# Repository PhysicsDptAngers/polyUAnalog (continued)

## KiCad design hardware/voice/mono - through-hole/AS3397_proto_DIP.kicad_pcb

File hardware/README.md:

## Hardware Components of the polyUAnalog System

- **Voice Board**: This is the core component of the project. A voice board is, by itself, an analog monophonic synthesizer. In short, the sound is generated by the AS3397 chip, controlled by an RP2040/RP2530 (Raspberry Pi Pico) microcontroller.

- **Conductor Board**: All voice boards are connected to the conductor board. It receives commands from external sources in MIDI-compatible format and distributes them to the voice boards via the I²C bus.

- **Controller Board**: These are the interface panels of the synthesizer. They typically include potentiometers, encoders, LEDs, and screens used to program and control the synthesizer. The corresponding data is sent to the conductor board via the I²C bus.

- **Power Board**: The synthesizer requires three power rails to operate (+12V, +5V, -5V). We provide a simple design using a USB Type-C power block with Power Delivery support to supply a regulated +12V rail. The +5V and -5V rails are then generated using buck converters.

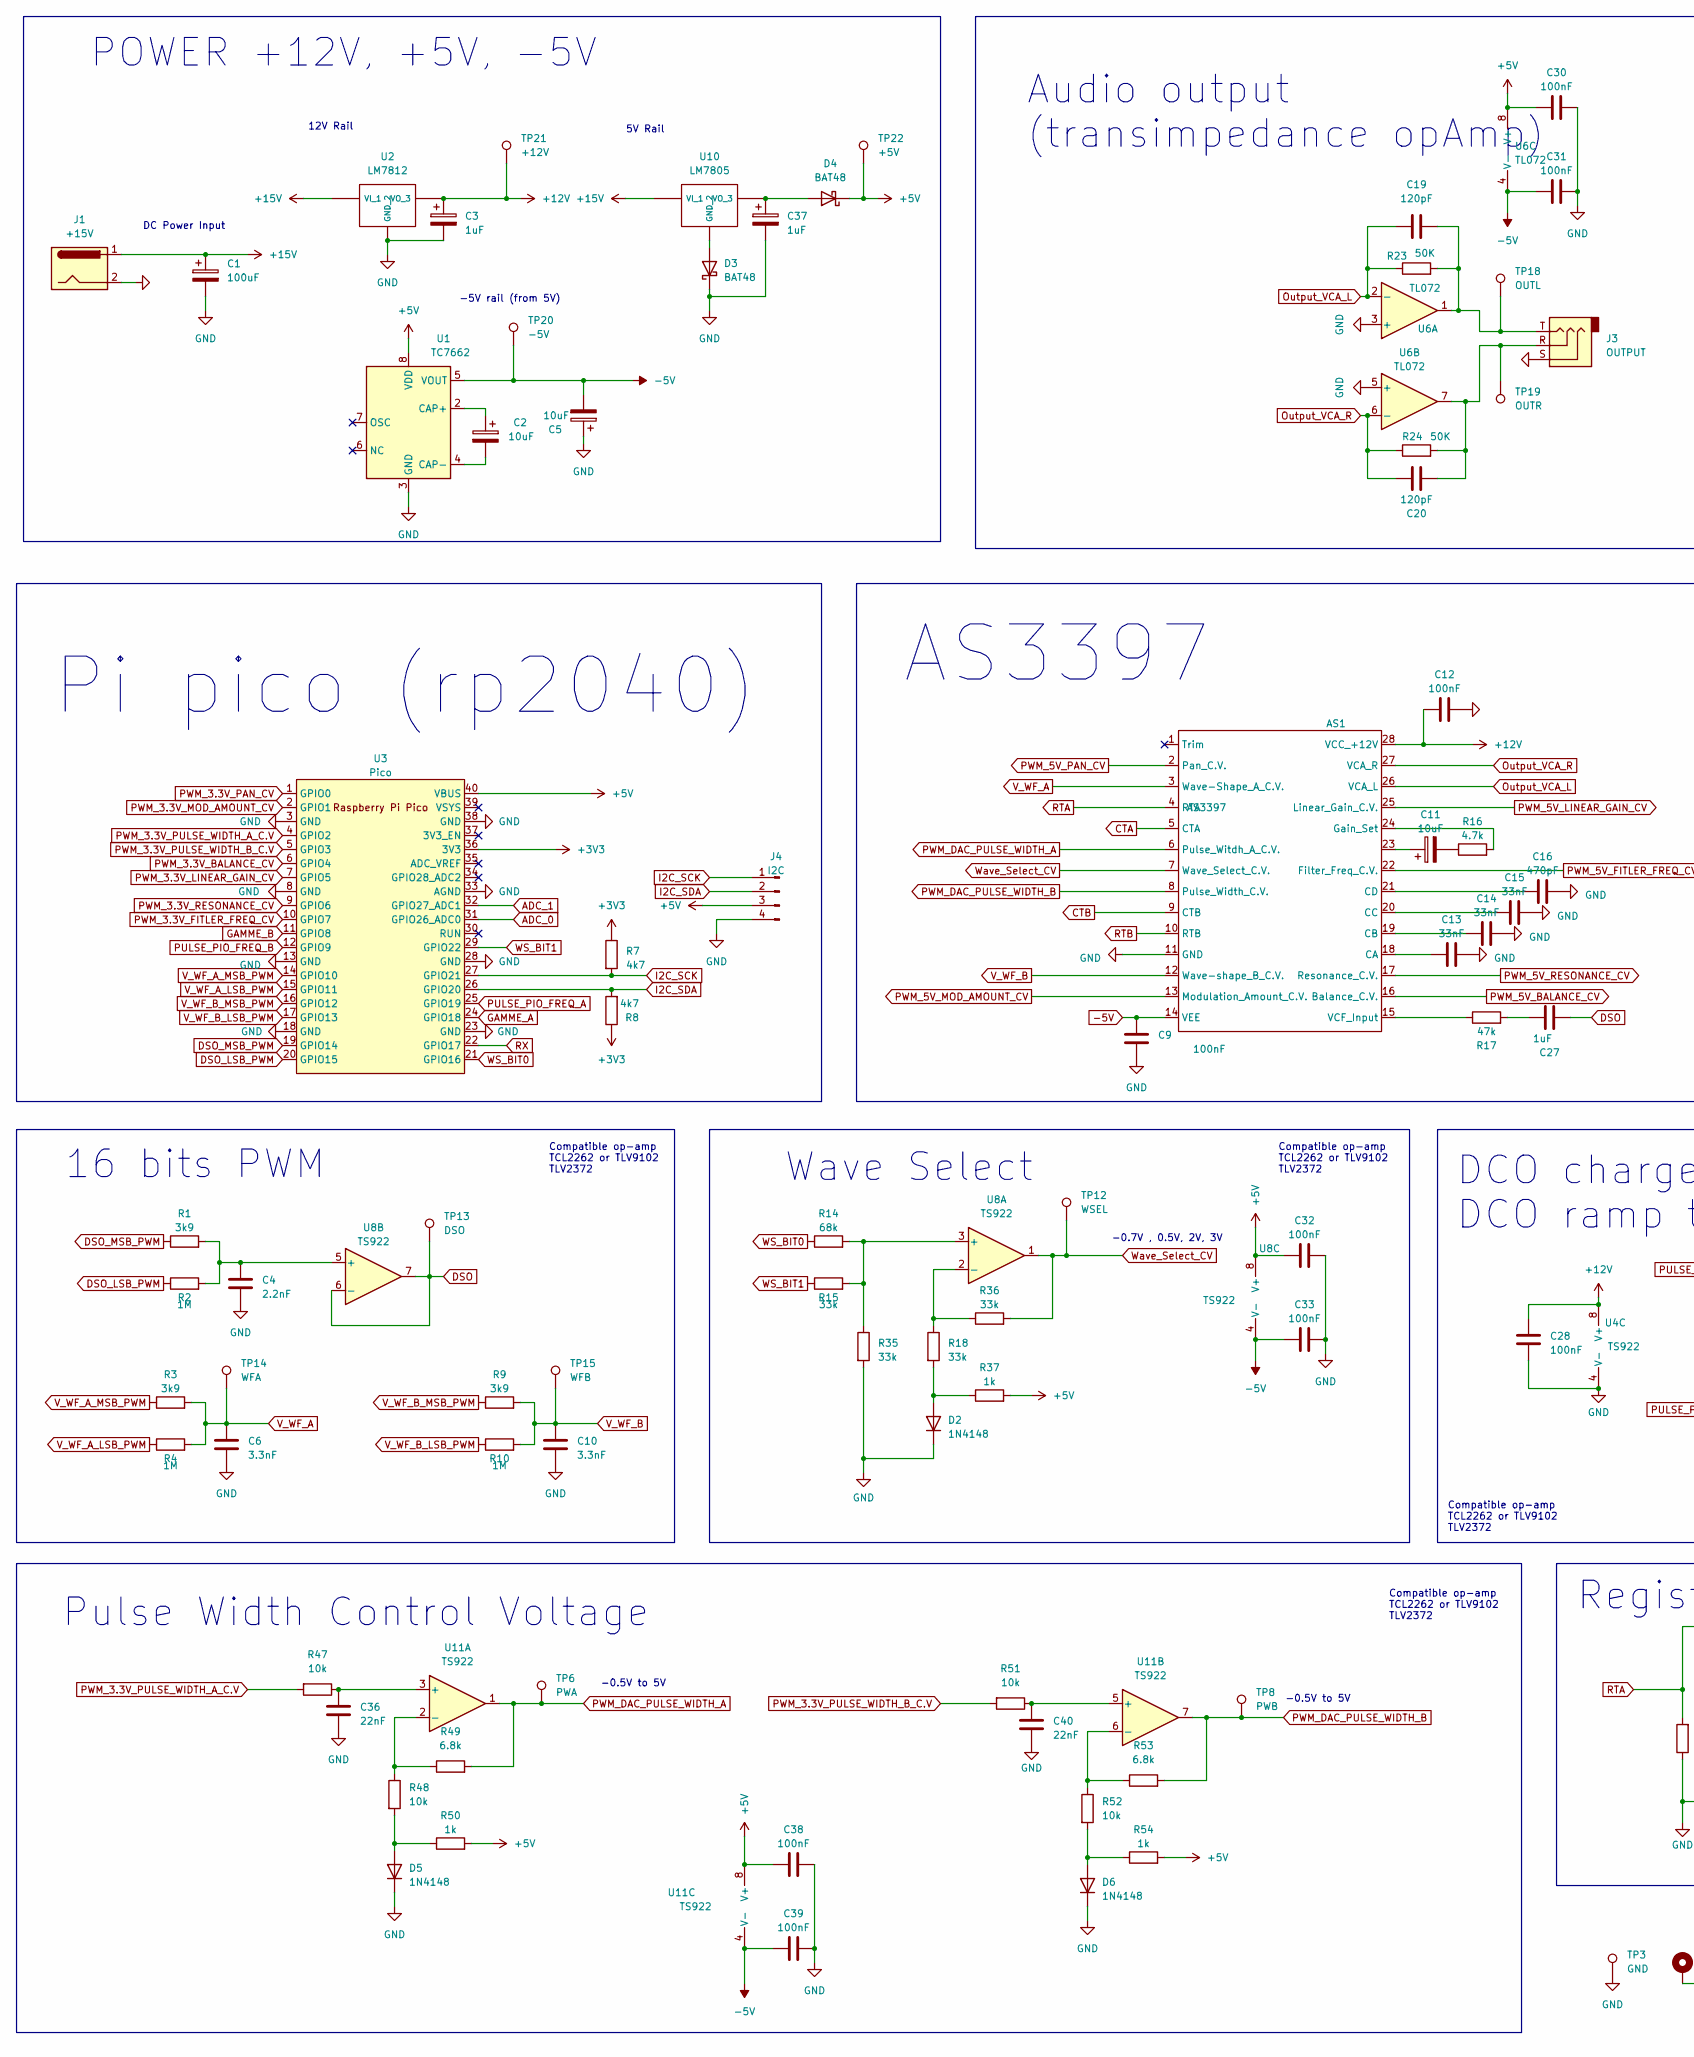
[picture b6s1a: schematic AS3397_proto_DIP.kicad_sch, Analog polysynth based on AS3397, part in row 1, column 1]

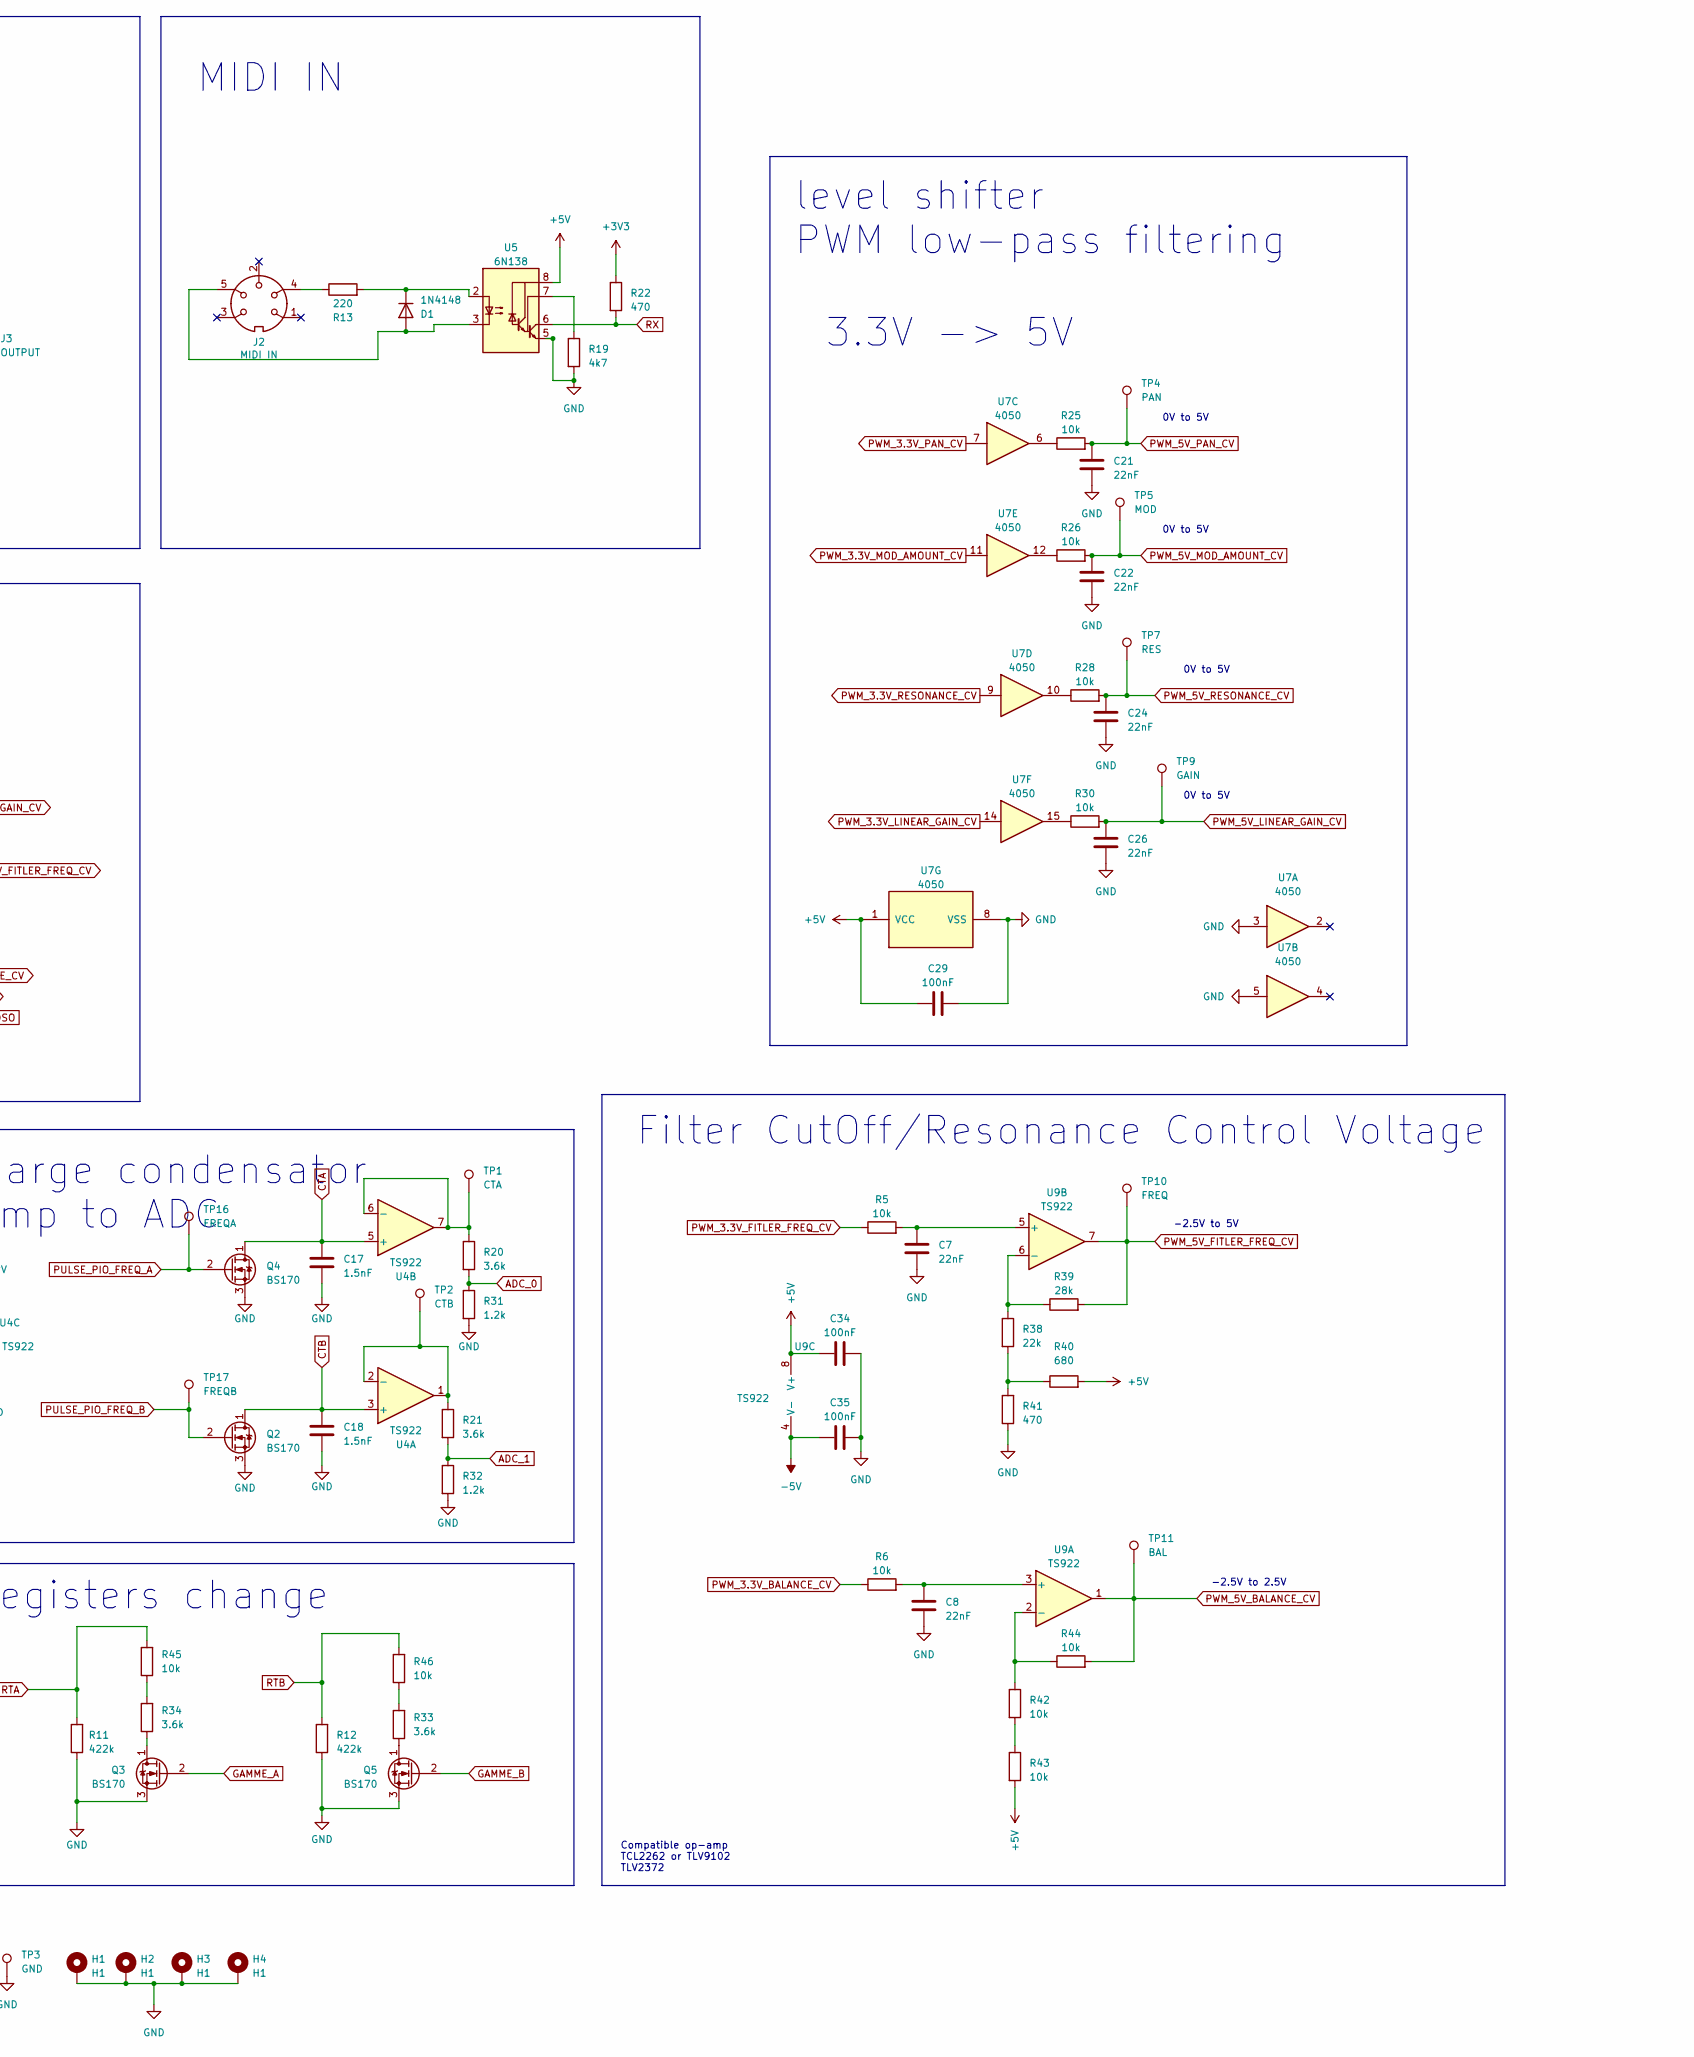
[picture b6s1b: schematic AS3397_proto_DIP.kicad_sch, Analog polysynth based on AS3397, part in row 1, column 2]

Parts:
AS1: AS3397; SOIC-28W_7.5x18.7mm_P1.27mm
C1: 100uF; CP_Radial_D8.0mm_P5.00mm
C2, C5, C11: 10uF; CP_Radial_D5.0mm_P2.50mm
C3, C37: 1uF; CP_Radial_D5.0mm_P2.50mm
C4: 2.2nF; C_Rect_L7.0mm_W2.0mm_P5.00mm
C6, C10: 3.3nF; C_Rect_L7.0mm_W2.0mm_P5.00mm
C7, C8, C21, C22, C24, C26, C36, C40: 22nF; C_Rect_L7.0mm_W2.0mm_P5.00mm
C9, C12, C28, C29, C30, C31, C32, C33, C34, C35, C38, C39: 100nF; C_Rect_L7.0mm_W2.0mm_P5.00mm
C13, C14, C15: 33nF; C_Rect_L7.0mm_W2.0mm_P5.00mm
C16: 470pF; C_Disc_D4.3mm_W1.9mm_P5.00mm
C17, C18: 1.5nF; C_Rect_L7.0mm_W2.0mm_P5.00mm
C19, C20: 120pF; C_Disc_D4.3mm_W1.9mm_P5.00mm
C27: 1uF; C_Rect_L7.0mm_W2.0mm_P5.00mm
D1, D2, D5, D6: 1N4148; D_DO-35_SOD27_P7.62mm_Horizontal
D3, D4: BAT48; D_DO-35_SOD27_P7.62mm_Horizontal
H1, H2, H3, H4: H1; MountingHole_3.2mm_M3_DIN965_Pad_TopBottom
J1: +15V; BarrelJack_Horizontal
J2: MIDI IN; MIDI_DIN5
J3: OUTPUT; Jack_3.5mm_Ledino_KB3SPRS_Horizontal
J4: I2C; NS-Tech_Grove_1x04_P2mm_Vertical
Q2, Q3, Q4, Q5: BS170; TO-92_Wide
R1, R3, R9: 3k9; R_Axial_DIN0204_L3.6mm_D1.6mm_P7.62mm_Horizontal
R2, R4, R10: 1M; R_Axial_DIN0204_L3.6mm_D1.6mm_P7.62mm_Horizontal
R5, R6, R25, R26, R28, R30, R42, R43, R44, R45, R46, R47, R48, R51, R52: 10k; R_Axial_DIN0204_L3.6mm_D1.6mm_P7.62mm_Horizontal
R7, R8, R19: 4k7; R_Axial_DIN0204_L3.6mm_D1.6mm_P7.62mm_Horizontal
R11, R12: 422k; R_Axial_DIN0204_L3.6mm_D1.6mm_P7.62mm_Horizontal
R13: 220; R_Axial_DIN0204_L3.6mm_D1.6mm_P7.62mm_Horizontal
R14: 68k; R_Axial_DIN0204_L3.6mm_D1.6mm_P7.62mm_Horizontal
R15, R18, R35, R36: 33k; R_Axial_DIN0204_L3.6mm_D1.6mm_P7.62mm_Horizontal
R16: 4.7k; R_Axial_DIN0204_L3.6mm_D1.6mm_P7.62mm_Horizontal
R17: 47k; R_Axial_DIN0204_L3.6mm_D1.6mm_P7.62mm_Horizontal
R20, R21, R33, R34: 3.6k; R_Axial_DIN0204_L3.6mm_D1.6mm_P7.62mm_Horizontal
R22, R41: 470; R_Axial_DIN0204_L3.6mm_D1.6mm_P7.62mm_Horizontal
R23, R24: 50K; R_Axial_DIN0204_L3.6mm_D1.6mm_P7.62mm_Horizontal
R31, R32: 1.2k; R_Axial_DIN0204_L3.6mm_D1.6mm_P7.62mm_Horizontal
R37, R50, R54: 1k; R_Axial_DIN0204_L3.6mm_D1.6mm_P7.62mm_Horizontal
R38: 22k; R_Axial_DIN0204_L3.6mm_D1.6mm_P7.62mm_Horizontal
R39: 28k; R_Axial_DIN0204_L3.6mm_D1.6mm_P7.62mm_Horizontal
R40: 680; R_Axial_DIN0204_L3.6mm_D1.6mm_P7.62mm_Horizontal
R49, R53: 6.8k; R_Axial_DIN0204_L3.6mm_D1.6mm_P7.62mm_Horizontal
TP1: CTA; PinHeader_1x01_P2.54mm_Vertical
TP2: CTB; PinHeader_1x01_P2.54mm_Vertical
TP3: GND; PinHeader_1x01_P2.54mm_Vertical
TP4: PAN; PinHeader_1x01_P2.54mm_Vertical
TP5: MOD; PinHeader_1x01_P2.54mm_Vertical
TP6: PWA; PinHeader_1x01_P2.54mm_Vertical
TP7: RES; PinHeader_1x01_P2.54mm_Vertical
TP8: PWB; PinHeader_1x01_P2.54mm_Vertical
TP9: GAIN; PinHeader_1x01_P2.54mm_Vertical
TP10: FREQ; PinHeader_1x01_P2.54mm_Vertical
TP11: BAL; PinHeader_1x01_P2.54mm_Vertical
TP12: WSEL; PinHeader_1x01_P2.54mm_Vertical
TP13: DSO; PinHeader_1x01_P2.54mm_Vertical
TP14: WFA; PinHeader_1x01_P2.54mm_Vertical
TP15: WFB; PinHeader_1x01_P2.54mm_Vertical
TP16: FREQA; PinHeader_1x01_P2.54mm_Vertical
TP17: FREQB; PinHeader_1x01_P2.54mm_Vertical
TP18: OUTL; PinHeader_1x01_P2.54mm_Vertical
TP19: OUTR; PinHeader_1x01_P2.54mm_Vertical
TP20: -5V; PinHeader_1x01_P2.54mm_Vertical
TP21: +12V; PinHeader_1x01_P2.54mm_Vertical
TP22: +5V; PinHeader_1x01_P2.54mm_Vertical
U1: TC7662; DIP-8_W7.62mm
U2: LM7812; TO-92_Inline_Wide
U3: Pico; RPi_Pico_SMD_TH
U4, U8, U9, U11: TS922; DIP-8_W7.62mm_LongPads
U5: 6N138; DIP-8_W7.62mm_LongPads
U6: TL072; DIP-8_W7.62mm_LongPads
U7: 4050; DIP-16_W7.62mm_LongPads
U10: LM7805; TO-220-3_Vertical

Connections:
+3V3: R7.1, R8.1, R22.1, U3.36 (3V3)
+5V: C29.1, C30.1, C32.1, C34.1, C38.1, D4.1 (K), J4.3, R37.2, R40.2, R43.2, R50.2, R54.2, TP22.1, U1.8 (VDD), U3.40 (VBUS), U5.8 (VCC), U6.8 (V+), U7.1 (VCC), U8.8 (V+), U9.8 (V+), U11.8 (V+)
+12V: AS1.28 (VCC_+12V), C3.1, C12.1, C28.2, TP21.1, U2.3 (VO), U4.8 (V+)
+15V: C1.1, J1.1, U2.1 (VI), U10.1 (VI)
-5V: AS1.14 (VEE), C5.2, C9.1, C31.1, C33.1, C35.1, C39.1, TP20.1, U1.5 (VOUT), U6.4 (V-), U8.4 (V-), U9.4 (V-), U11.4 (V-)
ADC_0: R20.2, R31.1, U3.31 (GPIO26_ADC0)
ADC_1: R21.2, R32.1, U3.32 (GPIO27_ADC1)
CTA: AS1.5 (CTA), C17.1, Q4.1 (D), U4.5 (+)
CTB: AS1.9 (CTB), C18.1, Q2.1 (D), U4.3 (+)
DSO: C27.2, TP13.1, U8.6 (-), U8.7
DSO_LSB_PWM: R2.1, U3.20 (GPIO15)
DSO_MSB_PWM: R1.1, U3.19 (GPIO14)
GAMME_A: Q3.2 (G), U3.24 (GPIO18)
GAMME_B: Q5.2 (G), U3.11 (GPIO8)
GND: AS1.11 (GND), C1.2, C3.2, C4.1, C5.1, C6.1, C7.2, C8.2, C9.2, C10.1, C12.2, C13.2, C14.1, C15.2, C16.2, C17.2, C18.2, C21.2, C22.2, C24.2, C26.2, C28.1, C29.2, C30.2, C31.2, C32.2, C33.2, C34.2, C35.2, C36.2, C37.2, C38.2, C39.2, C40.2, D2.1 (K), D3.1 (K), D5.1 (K), D6.1 (K), H1.1, H2.1, H3.1, H4.1, J1.2, J3.S, J4.4, Q2.3 (S), Q3.3 (S), Q4.3 (S), Q5.3 (S), R11.1, R12.1, R19.2, R31.2, R32.2, R35.2, R41.1, TP3.1, U1.3 (GND), U2.2 (GND), U3.3 (GND), U3.8 (GND), U3.13 (GND), U3.18 (GND), U3.23 (GND), U3.28 (GND), U3.33 (AGND), U3.38 (GND), U4.4 (V-), U5.5 (GND), U6.3 (+), U6.5 (+), U7.3, U7.5, U7.8 (VSS)
I2C_SCK: J4.1, R7.2, U3.27 (GPIO21)
I2C_SDA: J4.2, R8.2, U3.26 (GPIO20)
unnamed: AS1.18 (CA), C13.1
unnamed: AS1.19 (CB), C14.2
unnamed: AS1.20 (CC), C15.1
unnamed: AS1.21 (CD), C16.1
unnamed: AS1.24 (Gain_Set), R16.2
unnamed: AS1.23, C11.1
unnamed: AS1.15 (VCF_Input), R17.1
unnamed: C11.2, R16.1
unnamed: C19.2, J3.T, R23.2, TP18.1, U6.1
unnamed: C20.2, J3.R, R24.2, TP19.1, U6.7
unnamed: C27.1, R17.2
unnamed: D1.2 (A), J2.5, U5.3 (C2)
unnamed: D1.1 (K), R13.2, U5.2 (C1)
unnamed: D2.2 (A), R18.2, R37.1
unnamed: D3.2 (A), U10.2 (GND)
unnamed: C37.1, D4.2 (A), U10.3 (VO)
unnamed: D5.2 (A), R48.2, R50.1
unnamed: D6.2 (A), R52.2, R54.1
unnamed: J2.4, R13.1
unnamed: Q3.1 (D), R34.1
unnamed: Q5.1 (D), R33.1
unnamed: R25.1, U7.6
unnamed: R26.1, U7.12
unnamed: R28.1, U7.10
unnamed: R30.1, U7.15
unnamed: R33.2, R46.1
unnamed: R34.2, R45.1
unnamed: R38.2, R40.1, R41.2
unnamed: R42.2, R43.1
unnamed: C2.1, U1.2 (CAP+)
unnamed: C2.2, U1.4 (CAP-)
unnamed: R21.1, TP2.1, U4.1, U4.2 (-)
unnamed: R20.1, TP1.1, U4.6 (-), U4.7
unnamed: R19.1, U5.7 (VO1)
unnamed: R14.2, R15.2, R35.1, U8.3 (+)
unnamed: R18.1, R36.1, U8.2 (-)
unnamed: C4.2, R1.2, R2.2, U8.5 (+)
unnamed: C8.1, R6.2, U9.3 (+)
unnamed: R42.1, R44.1, U9.2 (-)
unnamed: C7.1, R5.2, U9.5 (+)
unnamed: R38.1, R39.1, U9.6 (-)
unnamed: C36.1, R47.1, U11.3 (+)
unnamed: R48.1, R49.1, U11.2 (-)
unnamed: C40.1, R51.1, U11.5 (+)
unnamed: R52.1, R53.1, U11.6 (-)
Output_VCA_L: AS1.26 (VCA_L), C19.1, R23.1, U6.2 (-)
Output_VCA_R: AS1.27 (VCA_R), C20.1, R24.1, U6.6 (-)
PULSE_PIO_FREQ_A: Q4.2 (G), TP16.1, U3.25 (GPIO19)
PULSE_PIO_FREQ_B: Q2.2 (G), TP17.1, U3.12 (GPIO9)
PWM_3.3V_BALANCE_CV: R6.1, U3.6 (GPIO4)
PWM_3.3V_FITLER_FREQ_CV: R5.1, U3.10 (GPIO7)
PWM_3.3V_LINEAR_GAIN_CV: U3.7 (GPIO5), U7.14
PWM_3.3V_MOD_AMOUNT_CV: U3.2 (GPIO1), U7.11
PWM_3.3V_PAN_CV: U3.1 (GPIO0), U7.7
PWM_3.3V_PULSE_WIDTH_A_C.V: R47.2, U3.4 (GPIO2)
PWM_3.3V_PULSE_WIDTH_B_C.V: R51.2, U3.5 (GPIO3)
PWM_3.3V_RESONANCE_CV: U3.9 (GPIO6), U7.9
PWM_5V_BALANCE_CV: AS1.16 (Balance_C.V.), R44.2, TP11.1, U9.1
PWM_5V_FITLER_FREQ_CV: AS1.22 (Filter_Freq_C.V.), R39.2, TP10.1, U9.7
PWM_5V_LINEAR_GAIN_CV: AS1.25 (Linear_Gain_C.V.), C26.1, R30.2, TP9.1
PWM_5V_MOD_AMOUNT_CV: AS1.13 (Modulation_Amount_C.V.), C22.1, R26.2, TP5.1
PWM_5V_PAN_CV: AS1.2 (Pan_C.V.), C21.1, R25.2, TP4.1
PWM_5V_RESONANCE_CV: AS1.17 (Resonance_C.V.), C24.1, R28.2, TP7.1
PWM_DAC_PULSE_WIDTH_A: AS1.6 (Pulse_Witdh_A_C.V.), R49.2, TP6.1, U11.1
PWM_DAC_PULSE_WIDTH_B: AS1.8 (Pulse_Width_C.V.), R53.2, TP8.1, U11.7
RTA: AS1.4 (RTA), R11.2, R45.2
RTB: AS1.10 (RTB), R12.2, R46.2
RX: R22.2, U3.22 (GPIO17), U5.6 (VO2)
V_WF_A: AS1.3 (Wave-Shape_A_C.V.), C6.2, R3.2, R4.2, TP14.1
V_WF_A_LSB_PWM: R4.1, U3.15 (GPIO11)
V_WF_A_MSB_PWM: R3.1, U3.14 (GPIO10)
V_WF_B: AS1.12 (Wave-shape_B_C.V.), C10.2, R9.2, R10.2, TP15.1
V_WF_B_LSB_PWM: R10.1, U3.17 (GPIO13)
V_WF_B_MSB_PWM: R9.1, U3.16 (GPIO12)
WS_BIT0: R14.1, U3.21 (GPIO16)
WS_BIT1: R15.1, U3.29 (GPIO22)
Wave_Select_CV: AS1.7 (Wave_Select_C.V.), R36.2, TP12.1, U8.1

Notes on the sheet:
16 bits PWM
Compatible op-amp TCL2262 or TLV9102 TLV2372
Registers change
-5V rail (from 5V)
5V Rail
POWER +12V, +5V, -5V
0V to 5V
Pulse Width Control Voltage
DCO charge condensator DCO ramp to ADC
AS3397
Wave Select
MIDI IN
DC Power Input
12V Rail
-0.7V , 0.5V, 2V, 3V
level shifter PWM low-pass filtering
Filter CutOff/Resonance Control Voltage
Pi pico (rp2040)
3.3V -> 5V
-0.5V to 5V
Audio output (transimpedance opAmp)
-2.5V to 2.5V
-2.5V to 5V

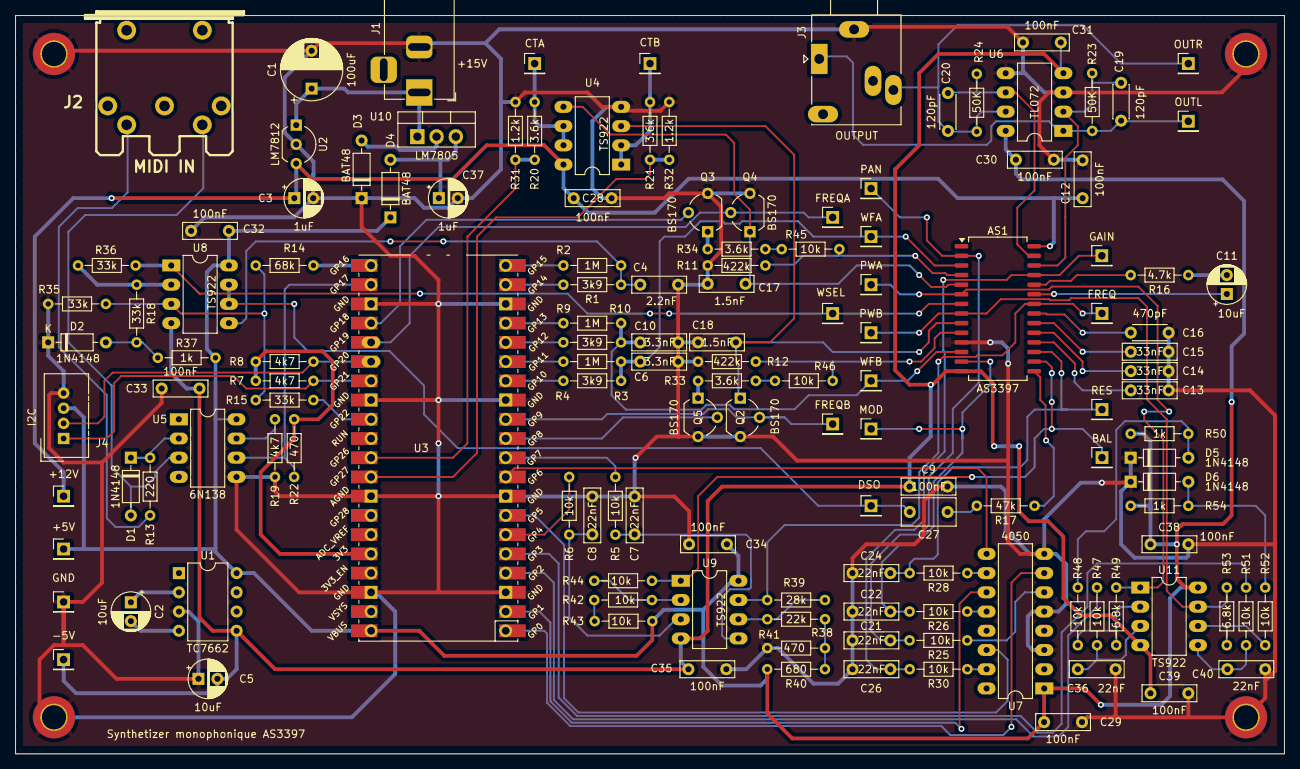
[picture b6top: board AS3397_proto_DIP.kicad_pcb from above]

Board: 2 copper layers, 167.6 x 97.5 mm, 142 parts (0 on the bottom side), 94 nets.

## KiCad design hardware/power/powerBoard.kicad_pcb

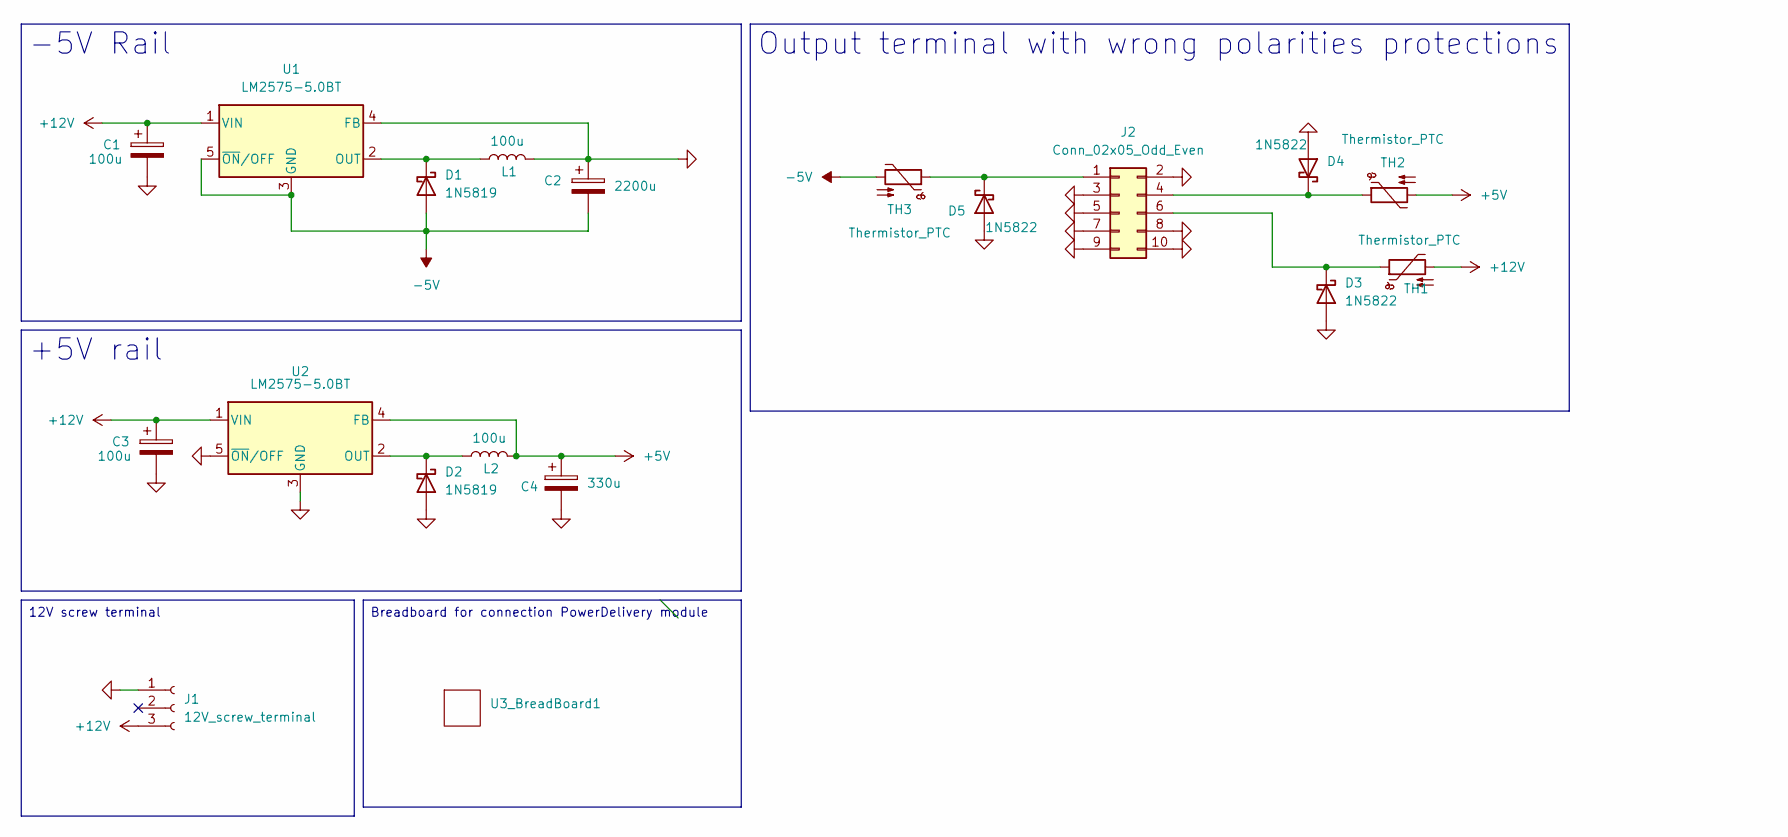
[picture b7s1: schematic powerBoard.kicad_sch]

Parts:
C1, C3: 100u; CP_Radial_D10.0mm_P5.00mm
C2: 2200u; CP_Radial_D10.0mm_P5.00mm
C4: 330u; CP_Radial_D10.0mm_P5.00mm
D1, D2: 1N5819; D_DO-41_SOD81_P10.16mm_Horizontal
D3, D4, D5: 1N5822; D_DO-201AD_P15.24mm_Horizontal
J1: 12V_screw_terminal; PinHeader_1x03_P2.54mm_Vertical
J2: Conn_02x05_Odd_Even; PinHeader_2x05_P2.54mm_Vertical
L1, L2: 100u; L_Radial_D12.5mm_P9.00mm_Fastron_09HCP
TH1, TH2, TH3: Thermistor_PTC; R_Axial_DIN0207_L6.3mm_D2.5mm_P7.62mm_Horizontal
U1, U2: LM2575-5.0BT; TO-220-5_Horizontal_TabDown
U3_BreadBoard1: BreadBoard

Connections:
+5V: C4.1, L2.2, TH2.2, U2.4 (FB)
+12V: C1.1, C3.1, J1.3, TH1.2, U1.1 (VIN), U2.1 (VIN)
-5V: C2.2, D1.2 (A), TH3.2, U1.3 (GND), U1.5 (~ON/OFF)
GND: C1.2, C2.1, C3.2, C4.2, D2.2 (A), D3.2 (A), D4.2 (A), D5.2 (A), J1.1, J2.2, J2.3, J2.5, J2.7, J2.8, J2.9, J2.10, L1.2, U1.4 (FB), U2.3 (GND), U2.5 (~ON/OFF)
unnamed: D1.1 (K), L1.1, U1.2 (OUT)
unnamed: D2.1 (K), L2.1, U2.2 (OUT)
unnamed: D3.1 (K), J2.6, TH1.1
unnamed: D4.1 (K), J2.4, TH2.1
unnamed: D5.1 (K), J2.1, TH3.1

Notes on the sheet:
12V screw terminal
Output terminal with wrong polarities protections
+5V rail
Breadboard for connection PowerDelivery module
-5V Rail

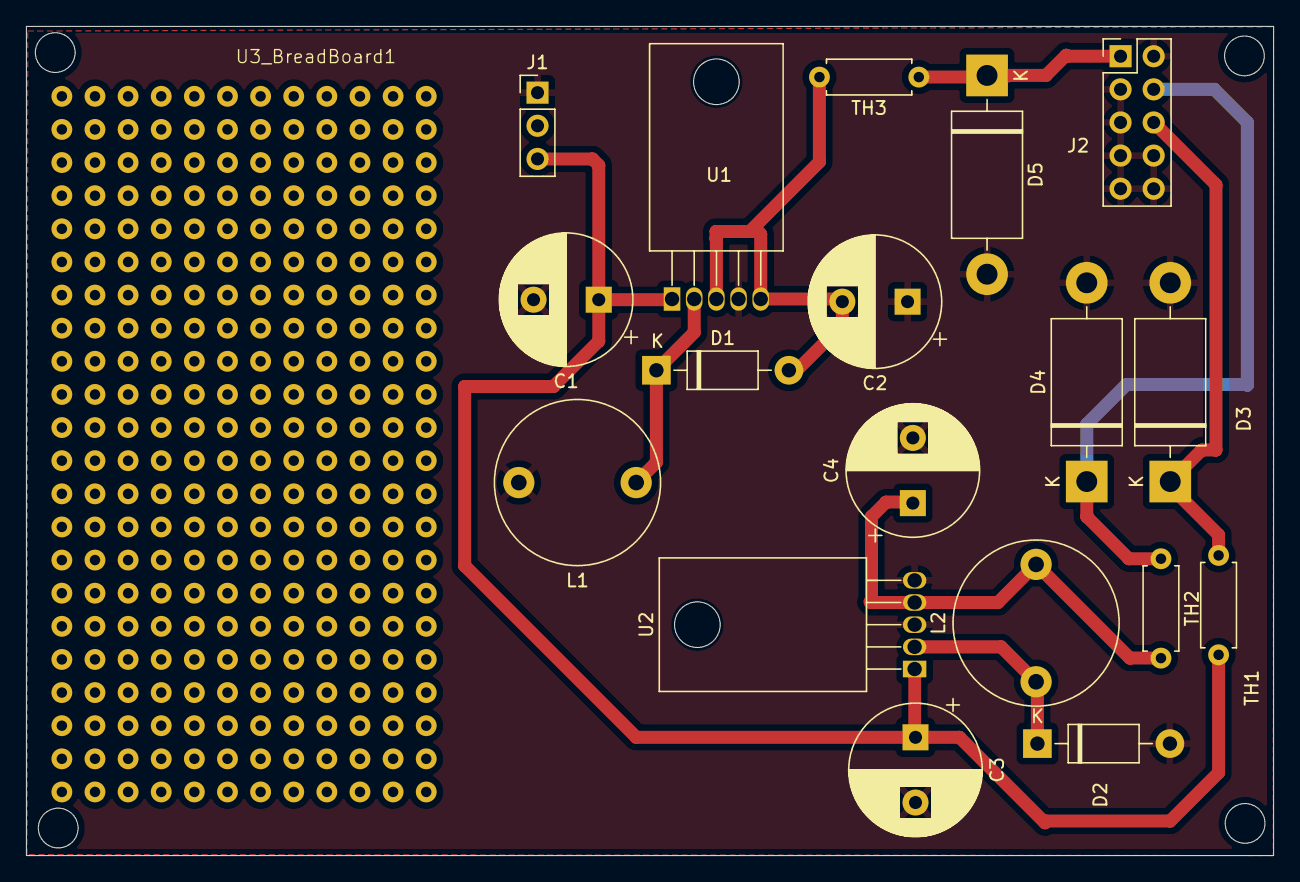
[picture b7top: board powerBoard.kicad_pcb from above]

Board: 2 copper layers, 95.6 x 63.6 mm, 19 parts (0 on the bottom side), 9 nets.

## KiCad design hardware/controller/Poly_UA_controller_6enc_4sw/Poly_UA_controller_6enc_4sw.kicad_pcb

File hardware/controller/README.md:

## Controller Board

The controller board serves as the equivalent of a synthesizer’s front panel.

For now, we provide a very basic frontend for a subtractive synthesizer. It is more of a demonstration of what can be done than a de facto standard. You can, in principle, design any frontend you like.

The controller board must send its data in MIDI format over the I²C bus to the conductor board.

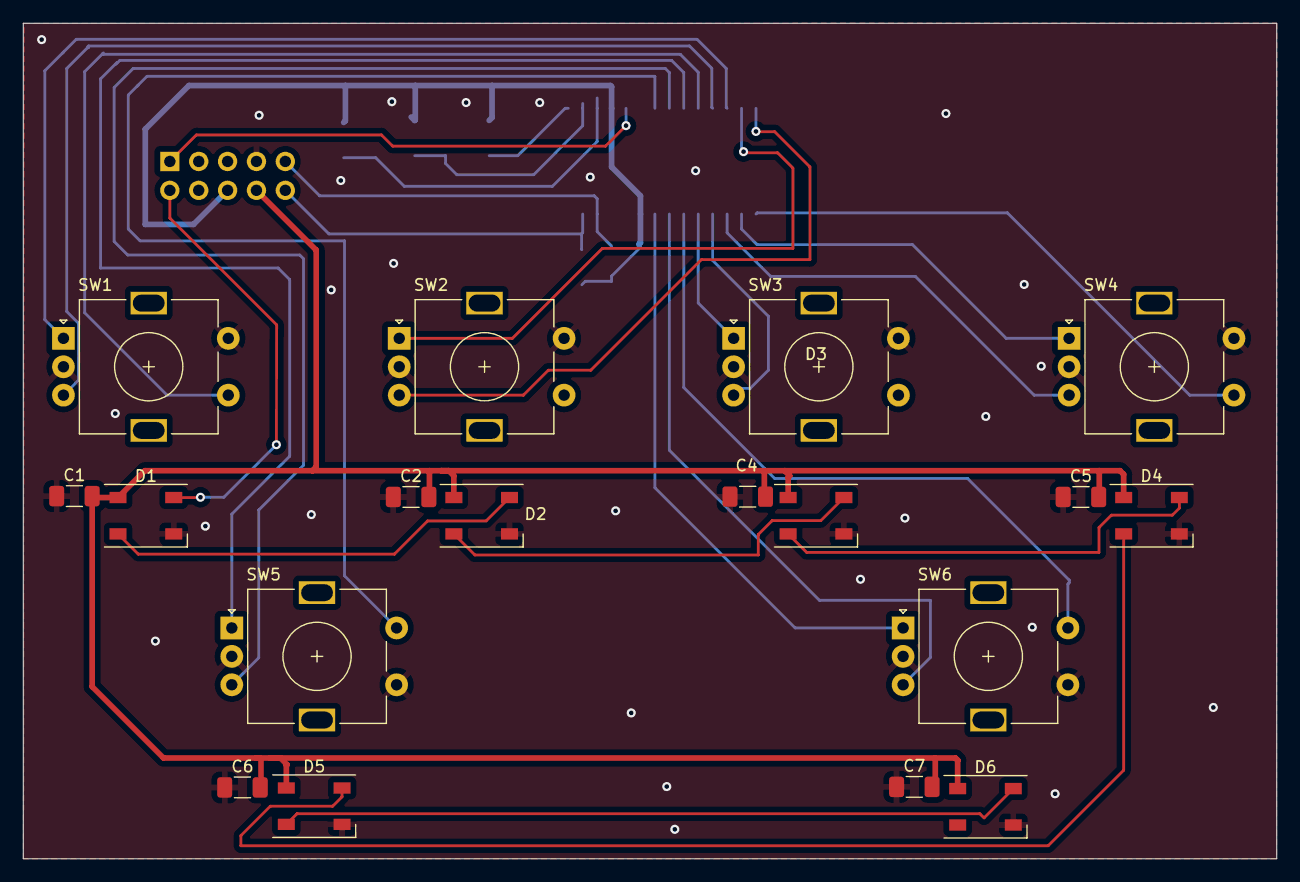
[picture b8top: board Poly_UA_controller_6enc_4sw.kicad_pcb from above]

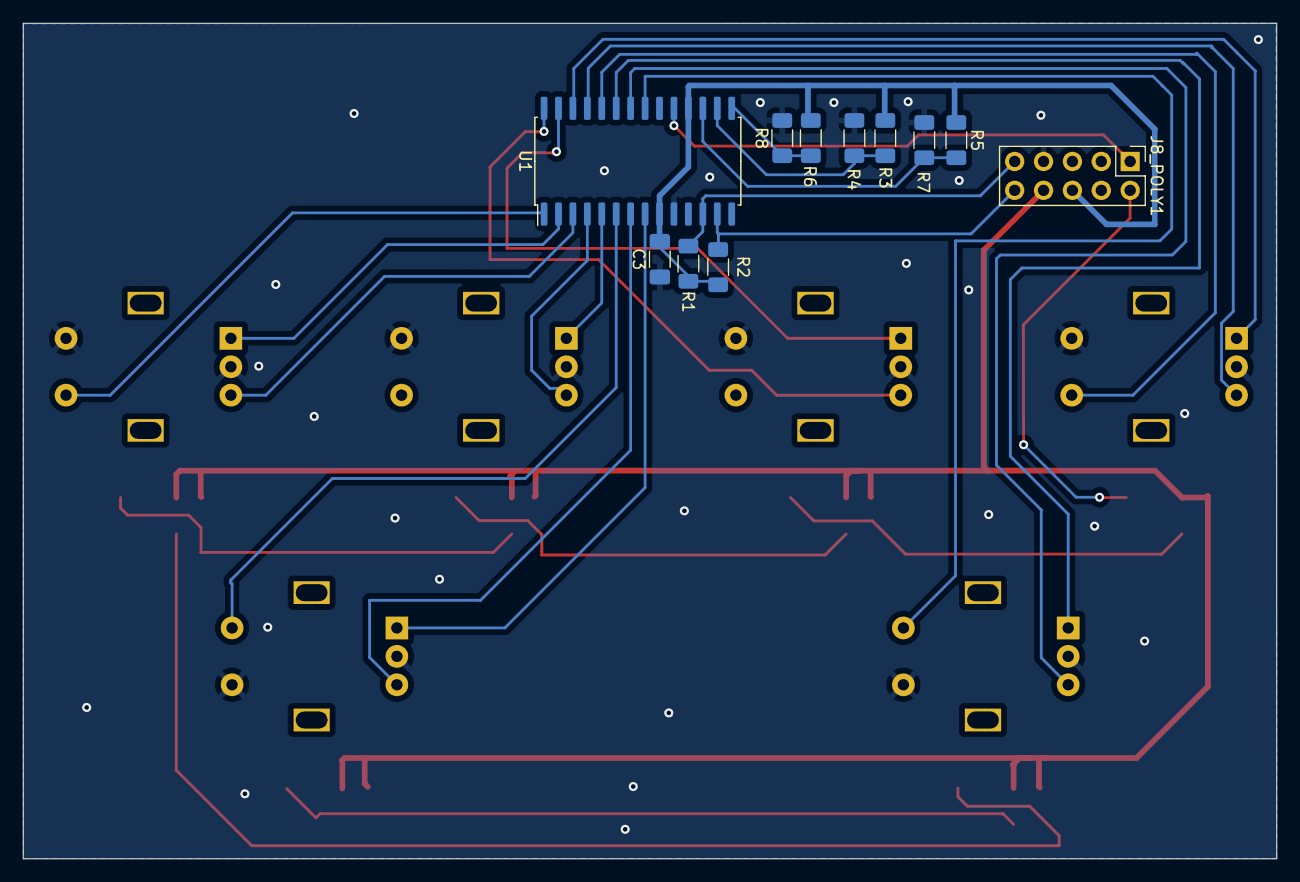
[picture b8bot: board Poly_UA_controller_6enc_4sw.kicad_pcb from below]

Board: 2 copper layers, 110.3 x 73.5 mm, 29 parts (11 on the bottom side), 31 nets.

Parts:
C1, C2, C4, C5, C6, C7: 100n; C_1206_3216Metric_Pad1.33x1.80mm_HandSolder
C3: C; C_1206_3216Metric_Pad1.33x1.80mm_HandSolder
D1, D2, D3, D4, D5, D6: SK6812; LED_SK6812_PLCC4_5.0x5.0mm_P3.2mm
J8_POLY1: Conn_Env; PinHeader_2x05_P2.54mm_Vertical
R1, R2: 4K7; R_1206_3216Metric_Pad1.30x1.75mm_HandSolder
R3, R4, R5, R6, R7, R8: 0; R_1206_3216Metric_Pad1.30x1.75mm_HandSolder
SW1, SW2, SW3, SW4, SW5, SW6: RotaryEncoder_Switch; RotaryEncoder_Alps_EC11E-Switch_Vertical_H20mm
U1: MCP23017_SO; SOIC-28W_7.5x17.9mm_P1.27mm

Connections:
GND: C1.1, C2.1, C3.1, C4.1, C5.1, C6.1, C7.1, D1.1 (VSS), D2.1 (VSS), D3.1 (VSS), D4.1 (VSS), D5.1 (VSS), D6.1 (VSS), J8_POLY1.7, R4.2, R7.2, R8.2, SW1.C, SW1.S2, SW2.C, SW2.S2, SW3.C, SW3.S2, SW4.C, SW4.S2, SW5.C, SW5.S1, SW6.C, SW6.S1, U1.10 (VSS)
LED_DATA_IN: D1.2 (DIN), J8_POLY1.2
LED_POWER: C1.2, C2.2, C4.2, C5.2, C6.2, C7.2, D1.3 (VDD), D2.3 (VDD), D3.3 (VDD), D4.3 (VDD), D5.3 (VDD), D6.3 (VDD), J8_POLY1.8
MCP23017_IRQ: J8_POLY1.1, U1.19 (INTB)
unnamed: D1.4 (DOUT), D2.2 (DIN)
unnamed: D2.4 (DOUT), D3.2 (DIN)
unnamed: D3.4 (DOUT), D4.2 (DIN)
unnamed: D4.4 (DOUT), D5.2 (DIN)
unnamed: D5.4 (DOUT), D6.2 (DIN)
unnamed: R6.2, R8.1, U1.15 (A0)
unnamed: R3.2, R4.1, U1.16 (A1)
unnamed: R5.2, R7.1, U1.17 (A2)
R1_A: SW1.A, U1.26 (GPA5)
R1_B: SW1.B, U1.25 (GPA4)
R2_A: SW2.A, U1.27 (GPA6)
R2_B: SW2.B, U1.28 (GPA7)
R3_A: SW3.A, U1.5 (GPB4)
R3_B: SW3.B, U1.4 (GPB3)
R4_A: SW4.A, U1.2 (GPB1)
R4_B: SW4.B, U1.3 (GPB2)
R5_A: SW5.A, U1.23 (GPA2)
R5_B: SW5.B, U1.22 (GPA1)
R6_A: SW6.A, U1.8 (GPB7)
R6_B: SW6.B, U1.7 (GPB6)
SCK: J8_POLY1.9, R2.1, U1.12 (SCK)
SDA: J8_POLY1.10, R1.2, U1.13 (SDA)
SW_1: SW1.S1, U1.24 (GPA3)
SW_4: SW4.S1, U1.1 (GPB0)
SW_5: SW5.S2, U1.21 (GPA0)
SW_6: SW6.S2, U1.6 (GPB5)
VCC: C3.2, J8_POLY1.6, R1.1, R2.2, R3.1, R5.1, R6.1, U1.9 (VDD), U1.18 (~RESET)

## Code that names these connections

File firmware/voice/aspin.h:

#ifndef ASPIN_H
#define ASPIN_H
// Définition des broches d'entrée sortie

#define VWFA_MSB_CV 10
#define VWFA_LSB_CV 11
#define VWFB_MSB_CV 12
#define VWFB_LSB_CV 13
#define DCOA_PW_CV 2
#define DCOB_PW_CV 3
#define BALANCE_CV 4

#define MOD_AMOUNT_CV 1
#define FILTER_FREQ_CV 7
#define FILTER_RES_CV 6

#define VCA_CV 5
#define PAN_CV 0

#define DSO_MSB 14
#define DSO_LSB 15

#define DCOA_FREQ 19
#define DCOB_FREQ 9
#define GAMME_A 18
#define GAMME_B 8

#define WS_BIT0 16
#define WS_BIT1 22

#define INPUT_RAMPE_A 0
#define INPUT_RAMPE_B 1

#define I2C_ADR_READ 2

#define MIDI_RX 17

// Définition des constantes pour le calcul de la rampe et de la fréquence
const float Rt = 13200;
const float Ct = 1.8E-9;
const uint8_t RampeDivisor = 4;
const float convFactor = (RampeDivisor * 3.3) / 4096;

//Gains du PI Kp et Ki
const float Kp = Rt * Ct * 16 * RampeDivisor;  //Le x16 c'est pour passer de 12bits (ADC In) à 16bits (PWM out)
const float Ki = 100;

// Définition des constantes pour le PWM
const int PWMRes = 256;
const int PWMResFilter = 16384;
const int PWMResVCA = 4096;

// Définition des constantes pour le Wave select control
#define WAVE_NONE 0
#define WAVE_A 1
#define WAVE_B 2
#define WAVE_AB 3

#endif

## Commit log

2024-04-18 better documentation
2024-04-26 Draft Article without todo list in french
2024-05-02 DCO documentation, Roadmap
2024-05-02 More DCO documentation
2024-05-06 DCO documentation - Waveshapper, Square wave
2025-03-04 New readme file for the voice firmware
2025-03-12 Added doxygen doc for voice firmware
2025-03-17 Voice PCB directory cleanup
2025-03-17 Voice PCB directory cleanup bis
2025-03-25 Power board
2025-03-25 hardware readme
2025-04-08 Through hole voice board first commit
2025-04-24 Voice firmware big improvement and through hole board fixes
2026-01-16 Conductor board new version
2026-01-22 Fixing routing power rail in conductor board
2026-01-23 Conductor Board : Fixing MIDI routing
2026-03-04 Modif of voice board smd and Cleanup
